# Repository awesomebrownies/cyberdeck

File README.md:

# cyberdeck

A portable cyberdeck designed around accessories and working on the move.

***Why?***
There are many game consoles out there, like the nintendo switch, and the steamdeck. I find the integrated controllers with the screen to be awesome for portability, while lacking in quality compared to standalone controllers. So? I created a high quality controller, connected comfortably to the screen. The cyberdeck in particular, has a interesting feature I wanted to tackle for true portability. **The keyboard.** Unlike a traditional laptop, which requires to be unfolded and set on a surface, the portable cyberdeck can type on the move. Using hand tracking algorithms, it can type different keystrokes, depending on the set distance ones fingers move. The picatinny rails attach to slings further complimenting this approach.

## Key features
* **Controllers**
  * 4x Distance Sensors (Hand Tracking): Predictive Steganography & normal typing switch
  * Joystick & Scroll Wheel: Moving cursor, scrolling, zooming & typing
  * Analog Trigger + Buttons: Clicks & keybinds
* **Shock Cage**
  * Springs can withstand <0.75m drop, rubber grommets for additional acceleration damping.
* **Travel Mode**
  * Foldable controllers on both sides for compact travel
  * When deployed: Space for a cooling fan, lowered controllers used as a stand, & space between controller & main body to strap to arm for carrying
* **Picatinny Rails**:
  * Used to attach custom gadgets to the device. Ex: Gun sling, or 3d printed mount
* **Physical Toggle Switches**
  * Toggle power & battery, software modes

## How to Assemble

There are three parts to this.
* Ordering BOM
* Fabricating PCB
* 3d Printing Parts (Check CAD folder)
* Putting it together

I figure most can get the first three done, but I'll go into detail for putting it together.

### Soldering the controller board

You can *in theory* solder this by hand, but I'd recommend using a **hot plate** to put on the **distance sensors** since they have ***tiny*** pads.
* Apply solder paste
* Heat the board on the pad

Next you'll put on the **joystick** and the other **non-SMD components**, including the buttons. A tip for the buttons is to only **solder diagonal pins** (look at the adafruit page video for more details).

Lastly, the Raspberry Pi Pico will go on. You'll want to **solder** on the **female pins** before putting on the board, so if it ever gets fried, or you want to take it off for some reason, it's super easy. Once the female pins have been soldered on the board, you just have to solder the male pins on the Raspberry Pi Pico, and attach it all together!

### Final Steps

From here on out, it's just two things.

1. Flashing firmware
2. Connecting to the main board

Connecting to the main board consists of the two power cables (+5v AND GND), and the **UART half-duplex** cable. Reference your Raspberry Pi pinout for more details on which pins to connect. It may vary per model, and you may already have some of the pins connected to other components. (This cyberdeck can act as a server when not in use)

To flash the firmware, open up the Arduino IDE, and copy and paste the code from the repository to both picos.

## Showcase

*Controller PCB*

*Controller Schematic*

*Cyberdeck Shock Cage* 

*Cyberdeck Overview*

## Build

# Project Bill of Materials

**Total Cost: $311.36**

## Main Body - $198.55

### Computing - $20.00

| Component                   | Quantity | Price  | Link                                                                                  | Notes             |
| --------------------------- | -------- | ------ | ------------------------------------------------------------------------------------- | ----------------- |
| Raspberry Pi 5 8GB          | 1        | -      | -                                                                                     | Already purchased |
| Top+Bottom Passive Heatsink | 1        | $7.00  | [Digikey](https://www.digikey.com/en/products/detail/edatec/ED-PI5CASE-OS/21769633)   |                   |
| 5V 5A Power Supply          | 1        | $13.00 | [Amazon](https://www.amazon.com/GeeekPi-Power-Supply-Raspberry-Adapter/dp/B0CQ2DL2RW) |                   |

### Hotswap Connectors & Controller Folding System - $13.42

| Component              | Quantity | Price | Link                                                                                                              | Notes |
| ---------------------- | -------- | ----- | ----------------------------------------------------------------------------------------------------------------- | ----- |
| 200mm Metal Rods       | 2        | $5.04 | [AliExpress](https://www.aliexpress.us/item/3256806550938490.html)                                                |       |
| Spring Loaded Contacts | 6        | $3.96 | [Digikey](https://www.digikey.com/en/products/detail/mill-max-manufacturing-corp/0906-2-15-20-75-14-11-0/1147050) |       |
| Small Magnets          | 14       | $4.42 | [Digikey](https://www.digikey.com/en/products/detail/radial-magnets-inc/8193/555328)                              |       |

### Shock Cage - $18.98

| Component | Quantity | Price | Link                                                                                                                     | Notes |
| --------- | -------- | ----- | ------------------------------------------------------------------------------------------------------------------------ | ----- |
| Springs   | 16       | $8.99 | [Amazon](https://www.amazon.com/Dianrui-Compression-Assortment-Mechanical-K-P-051-300/dp/B0BVTDP29W/143-1548753-7471335) |       |
| Grommets  | 16       | $9.99 | [Amazon](https://www.amazon.com/200PCS-Grommet-Electrical-Firewall-Assortment/dp/B08CD9KGHN)                             |       |

### Mesh Arm Mount - $5.00

| Component | Quantity | Price | Link                                                                                                                     | Notes           |
| --------- | -------- | ----- | ------------------------------------------------------------------------------------------------------------------------ | --------------- |
| Mesh      | 1        | $5.00 | [Walmart](https://www.walmart.com/ip/Polyester-Knit-Diamond-Mesh-Fabric-Black-Sheer-Polyester-63-By-The-Yard/2555999935) | Local catalogue |

### Other Components - $141.15

| Component           | Quantity | Price  | Link                                                                                            | Notes                                        |
| ------------------- | -------- | ------ | ----------------------------------------------------------------------------------------------- | -------------------------------------------- |
| Toggle Switch       | 5        | -      | -                                                                                               | Already own                                  |
| Display             | 1        | $67.50 | [eBay](https://www.ebay.com/itm/267231078389)                                                   |                                              |
| Heat Set Inserts    | 50       | $7.39  | [Digikey](https://www.digikey.com/en/products/detail/tri-star-industries-inc/M20X157C/13535373) |                                              |
| M2 Screws           | 1 set    | $12.99 | [Amazon](https://www.amazon.com/DYWISHKEY-Pieces-Stainless-Phillips-Screws/dp/B07W5J4WC9)       |                                              |
| PETG Plastic Spool  | 1        | $18.00 | -                                                                                               | For 3D printing, local printer reimbursement |
| Battery             | 1        | $26.97 | [Amazon](https://www.amazon.com/INIU-Portable-20000mAh-High-speed-Flashlight/dp/B07YPY31FL)     |                                              |
| Voltage Regulator   | 1        | $5.30  | [Digikey](https://www.digikey.com/en/products/detail/dfrobot/DFR1015/18069278)                  |                                              |
| USB-C PD Negotiator | 1        | $3.00  | [AliExpress](https://www.aliexpress.us/item/3256806276110723.html)                              |                                              |

## Controller - $112.81

### Main Components - $100.36

| Component                     | Quantity | Price  | Link                                                                                                | Notes |
| ----------------------------- | -------- | ------ | --------------------------------------------------------------------------------------------------- | ----- |
| JH16 Joystick                 | 2        | $11.01 | [AliExpress](https://www.aliexpress.com/i/3256808274885275.html)                                    |       |
| Hall Effect Sensor            | 2        | $2.30  | [Digikey](https://www.digikey.com/en/products/detail/allegro-microsystems/A1315LLHLX-5-T/8032467)   |       |
| Soft Tactile Switch           | 4        | $1.95  | [Adafruit](https://www.adafruit.com/product/3101)                                                   |       |
| Rotary Encoder                | 2        | $3.22  | [Digikey](https://www.digikey.com/en/products/detail/tt-electronics-bi/EN12-VN20AF20/2408775?gQT=2) |       |
| Mini Motor Disc               | 2        | $8.16  | [Adafruit](https://www.adafruit.com/product/1201)                                                   |       |
| Raspberry Pi Pico             | 2        | $19.16 | [Adafruit](https://www.adafruit.com/product/5544)                                                   |       |
| PCB                           | 2        | $18.89 | JLCPCB                                                                                              |       |
| I2C Distance Sensor (VL6180X) | 10       | $32.05 | [Digikey](https://www.digikey.com/en/products/detail/stmicroelectronics/VL53L4CDV0DH-1/16123783)    |       |
| Op-Amp                        | 4        | $1.52  | [Digikey](https://www.digikey.com.br/en/products/detail/texas-instruments/LMV358IDR/381251)         |       |
| Linear Regulator              | 2        | $1.36  | [Digikey](https://www.digikey.com/en/products/detail/umw/AMS1117-3-3/17635254)                      |       |
| 180kΩ SM Resistor             | 4        | $0.40  | [Digikey](https://www.digikey.com/en/products/detail/yageo/RC0603JR-07180KL/726723)                 |       |
| 330kΩ SM Resistor             | 4        | $0.40  | [Digikey](https://www.digikey.com/en/products/detail/yageo/RC0603JR-07330KL/726770)                 |       |

### Knuckle Straps - $12.45

| Component                   | Quantity | Price | Link                                                                                                                     | Notes |
| --------------------------- | -------- | ----- | ------------------------------------------------------------------------------------------------------------------------ | ----- |
| Cloth                       | 2        | $3.97 | [Walmart](https://www.walmart.com/ip/Dritz-Hanked-Non-Roll-Woven-Elastic-Black-Sewing-Fasteners/5226743025)              |       |
| Spring Loaded Cord Fastener | 2        | $3.00 | [Amazon](https://www.amazon.com/Cord-Upgraded-Fastener-Shoelaces-Drawstrings/dp/B08JTZPQRY)                              |       |
| Paracord                    | 1        | $5.48 | [Walmart](https://www.walmart.com/ip/Ozark-Trail-50-Foot-1100lbs-Paracord-Rope-100-Polyester-Black-Model-2112/311952813) |       |

---

## Cost Summary

| Section    | Cost        |
| ---------- | ----------- |
| Main Body  | $198.55     |
| Controller | $112.81     |
| **Total**  | **$311.36** |

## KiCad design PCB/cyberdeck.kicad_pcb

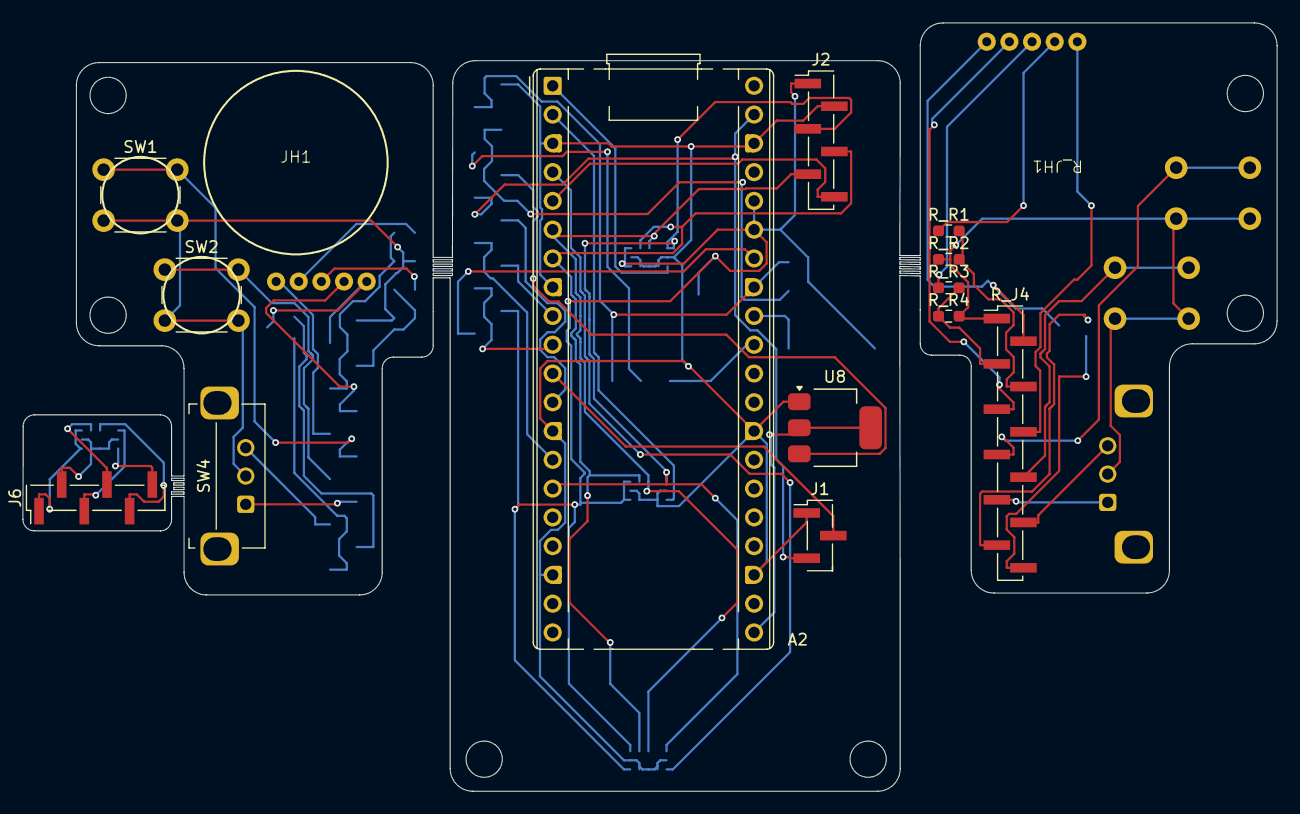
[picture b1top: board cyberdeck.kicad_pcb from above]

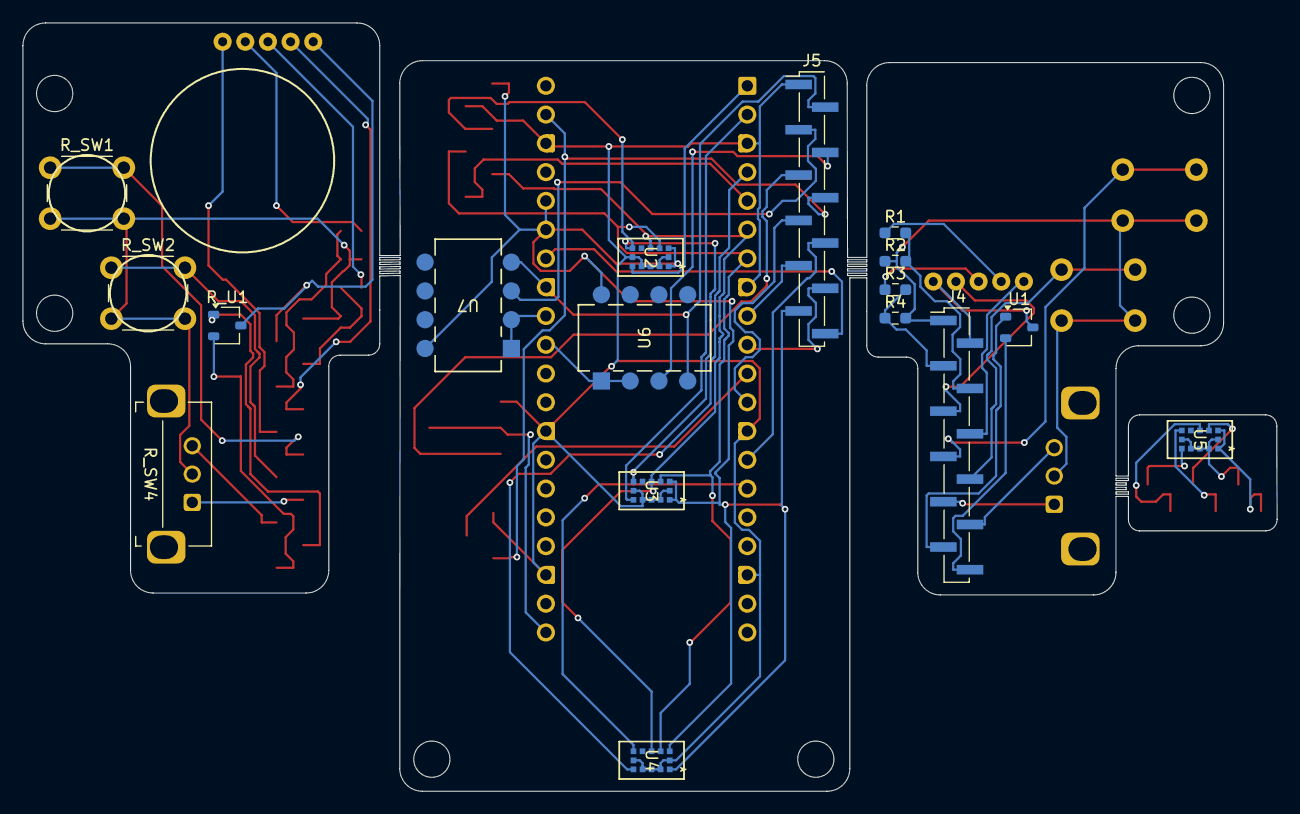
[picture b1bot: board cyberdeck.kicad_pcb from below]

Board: 2 copper layers, 110.7 x 67.8 mm, 38 parts (19 on the bottom side), 43 nets.

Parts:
A2: RaspberryPi_Pico_W; RaspberryPi_Pico_Common_THT
J1: Conn_01x03; PinHeader_1x03_P2.00mm_Vertical_SMD_Pin1Left
J2, J6: Conn_01x06; PinHeader_1x06_P2.00mm_Vertical_SMD_Pin1Left
J4, J5: Conn_01x12; PinHeader_1x12_P2.00mm_Vertical_SMD_Pin1Left
JH1: JH16
M1, M2, M3, M4, M5, M6: MountingHole_3.2mm_M3
R1, R2, R3, R4: R; R_0603_1608Metric_Pad0.98x0.95mm_HandSolder
R_J4: Conn_01x12; PinHeader_1x12_P2.00mm_Vertical_SMD_Pin1Left
R_JH1: JH16
R_R1, R_R2, R_R3, R_R4: R; R_0603_1608Metric_Pad0.98x0.95mm_HandSolder
R_SW1, R_SW2: SW_Push; SW_PUSH_6mm_H8mm
R_SW4: RotaryEncoder; RotaryEncoder_Bourns_Horizontal_PEC12R-2x17F-Nxxxx
R_U1: A1308xLHxx-1; SOT-23W
SW1, SW2: SW_Push; SW_PUSH_6mm_H8mm
SW4: RotaryEncoder; RotaryEncoder_Bourns_Horizontal_PEC12R-2x17F-Nxxxx
U1: A1308xLHxx-1; SOT-23W
U2, U3, U4, U5: VL53L4CDV0DH/1; LGA12_STM
U6, U7: LMV358; DIP8_300
U8: AMS1117-3.3; SOT-223-3_TabPin2

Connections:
+3.3V: A2.35 (ADC_VREF), A2.36 (3V3), J2.1, J5.11, U2.1 (AVDDVCSEL), U2.11 (AVDD), U3.1 (AVDDVCSEL), U3.11 (AVDD), U4.1 (AVDDVCSEL), U4.11 (AVDD), U6.8 (V+), U7.8 (V+)
A: A2.9 (GPIO6), J5.9
AGND: A2.33 (AGND), J5.2, U6.4 (V-), U7.4 (V-)
B: A2.10 (GPIO7), J5.10
D1_XSHUT: A2.1 (GPIO0), U2.5 (XSHUT)
D2_XSHUT: A2.2 (GPIO1), U3.5 (XSHUT)
D3_XSHUT: A2.4 (GPIO2), U4.5 (XSHUT)
D4_XSHUT: A2.5 (GPIO3), J2.6
DATA: A2.11 (GPIO8), J1.2
External 5v: A2.39 (VSYS), J1.3, J5.6
GND: A2.3 (GND), A2.8 (GND), A2.13 (GND), A2.18 (GND), A2.23 (GND), A2.28 (GND), A2.38 (GND), J1.1, J2.2, J5.1, U2.2 (AVSSVCSEL), U2.3 (GND), U2.4 (GN2), U2.6 (GND3), U2.12 (GND4), U3.2 (AVSSVCSEL), U3.3 (GND), U3.4 (GN2), U3.6 (GND3), U3.12 (GND4), U4.2 (AVSSVCSEL), U4.3 (GND), U4.4 (GN2), U4.6 (GND3), U4.12 (GND4), U8.1 (GND)
JH_SW: J5.5, U8.3 (VI)
J_3.3v: J4.11, R_J4.11, R_U1.1 (V_{CC}), U1.1 (V_{CC})
J_A: J4.9, R_J4.9, R_SW4.A, SW4.A
J_AGND: J4.2, JH1.5 (GND), R_J4.2, R_JH1.5 (GND), R_U1.3 (GND), U1.3 (GND)
J_B: J4.10, R_J4.10, R_SW4.B, SW4.B
J_External 5v: J4.6, JH1.1 (VCC), R_J4.6, R_JH1.1 (VCC)
J_GND: J4.1, R2.1, R4.2, R_J4.1, R_R2.1, R_R4.2, R_SW1.2, R_SW2.2, R_SW4.C, SW1.2, SW2.2, SW4.C
J_JH_SW: J4.5, JH1.4 (Switch), R_J4.5, R_JH1.4 (Switch)
J_SW1: J4.7, R_J4.7, R_SW1.1, SW1.1
J_SW2: J4.8, R_J4.8, R_SW2.1, SW2.1
J_Trigger_ADC: J4.12, R_J4.12, R_U1.2 (V_{OUT}), U1.2 (V_{OUT})
J_X_ADC: J4.4, R1.2, R2.2, R_J4.4, R_R1.2, R_R2.2
J_Y_ADC: J4.3, R3.2, R4.1, R_J4.3, R_R3.2, R_R4.1
unnamed: A2.15 (GPIO11), J2.3, U2.7 (GPIO1), U3.7 (GPIO1), U4.7 (GPIO1)
unnamed: A2.21 (GPIO16), U8.2 (VO)
unnamed: J5.3, U7.3 (+)
unnamed: J5.4, U6.3 (+)
unnamed: JH1.2 (X), R1.1, R_JH1.2 (X), R_R1.1
unnamed: JH1.3 (Y), R3.1, R_JH1.3 (Y), R_R3.1
SCL: A2.7 (GPIO5), J2.4, U2.10 (SCL), U3.10 (SCL), U4.10 (SCL)
SDA: A2.6 (GPIO4), J2.5, U2.9 (SDA), U3.9 (SDA), U4.9 (SDA)
SW1: A2.12 (GPIO9), J5.7
SW2: A2.14 (GPIO10), J5.8
T_3.3v: J6.1, U5.1 (AVDDVCSEL), U5.11 (AVDD)
T_D4_XSHUT: J6.6, U5.5 (XSHUT)
T_GND: J6.2, U5.2 (AVSSVCSEL), U5.3 (GND), U5.4 (GN2), U5.6 (GND3), U5.12 (GND4)
T_GPIO1: J6.3, U5.7 (GPIO1)
T_SCL: J6.4, U5.10 (SCL)
T_SDA: J6.5, U5.9 (SDA)
Trigger_ADC: A2.34 (GPIO28_ADC2), J5.12
X_ADC: A2.31 (GPIO26_ADC0), U6.1, U6.2 (-)
Y_ADC: A2.32 (GPIO27_ADC1), U7.1, U7.2 (-)

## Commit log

2025-05-18 Add journal and parts markdown
2025-06-18 Add step files
2025-06-18 Add PCB Folder
2025-06-18 Add BOM
2025-06-18 Upload kicad PCB files
2025-06-18 Right controller tweaks
2025-06-18 Change file name
2025-06-18 Add files & basic code
2025-06-18 Add VL53L4CD library
2025-06-18 Add vl53l4cd_sat prototype
2025-06-19 Tidy journal
2025-06-19 Add CAD instructions
2025-06-21 Add full assembly step file
